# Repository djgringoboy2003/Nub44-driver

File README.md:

# NUBM44 laser diode driver

A constant-current driver for the Nichia NUBM44 high-power blue laser diode, from a single Li-ion cell,
targeting a 22 mm round PCB (plus a larger evaluation board) for PCBWay fabrication and assembly. Designed in KiCad 10 from version-controlled sources
(parameters, connectivity, placement), with automated checks and manufacturing export.

> **Safety:** the NUBM44 is a Class 4 laser source. Bench work needs a dummy load first, then appropriate
> eyewear, interlocks and a controlled area. This design is **not** validated on hardware (Gate G open).

## Status

- **Evaluation board (Variant B, 45 × 40 mm):** CAD complete (DRC 0/0/0/0), power-layout reviewed, DRAFT PCBWay
  review package generated. Release readiness: **DRAFT_REVIEW**; it becomes a PROTOTYPE_CANDIDATE once five human
  footprint/orientation reviews are recorded (`engineering/release/design-reviews.yaml`). Orders are placed by the
  owner by hand.
- **Compact board (Variant A, Ø 22 mm):** routing draft with 20 open signal connections, parked until the
  evaluation prototype has produced bench data (owner decision DD-27; strategy in
  `engineering/pcb-review-2026-10-26.md`). Its fabrication ZIP carries `DO_NOT_FABRICATE.txt`.
- **Separate budget-2s driver:** owner accepts two series Li-ion cells, unrestricted size and a £60 target
  per working unit. Electrical qualification has started (DD-30): independent numeric sources, conditional
  calculations and a preliminary ngspice loop study. Efficiency, UVLO and fault-control issues remain OPEN;
  no budget PCB/manufacturing package exists. Continue from the
  [implementation handover](engineering/budget-2s-design.md) and [plan](engineering/budget-driver-plan.md).
- **Physical validation (Gate G):** not started; it needs an assembled prototype and recorded bench data.
- **Firmware:** reworked after an independent audit (DD-28); 531 host checks, register-model tests of the hardware
  layer and a mutation check; not yet run on hardware.

**Ordering:** files and options for PCBWay and JLCPCB are in [documentation/ordering-guide.md](documentation/ordering-guide.md);
the pre-order review brief is [documentation/pre-order-review.md](documentation/pre-order-review.md).

Live state: [PROGRESS.md](PROGRESS.md) and the generated dashboard `reports/dashboard/index.html` (open it in a
browser). Agents start with [AGENTS.md](AGENTS.md); people with the
[developer guide](documentation/developer-guide.md). Audit: [reports/comprehensive-project-audit.md](reports/comprehensive-project-audit.md).

## Key specifications (original A/B design targets; see `engineering/requirements.md` for status)

| Item | Value |
|---|---|
| Input | 1 × Li-ion, 2.83–4.2 V at the board (18650/21700, ≥ 15 A CDR recommended) |
| Output | Constant current, 4.5 A (owner decision DD-36; 3.0 / 3.5 / 4.0 A by one resistor), compliance about 0.8–22 V |
| Converter | TI TPS552882 4-switch buck-boost, 595 kHz, 1.0 µH |
| Current regulation | 10 mΩ high-side shunt, INA186A2, ±3.6 % worst case (calculated) |
| Protection | Reverse polarity (P-FET), hardware UVLO, 4.8–5.2 A hardware current ceiling, hiccup short protection, open-load trip, interlock, default-off enable, thermal monitoring |
| Modes | Continuous, flash (2 Hz default); mode change by short power interruption or optional switch pad |
| Efficiency (estimated, 4.5 A) | 94.1 % at 4.0 V by model, 93.6 % with routed copper (target ≥ 93 %, owner DD-37); 90.3 % at 3.0 V |
| PCB | 4 layers, 1.6 mm, ENIG: Ø 22 mm compact board (Variant A) and 45 × 40 mm evaluation board (Variant B) |

## Getting started

```powershell
.\scripts\setup.ps1          # installs/repairs the toolchain (no admin rights needed)
.venv\Scripts\python.exe -m pytest tests                               # unit tests
.venv\Scripts\python.exe firmware\build.py --mutation                  # firmware host tests, ATtiny1616 build, mutation check
.venv\Scripts\python.exe automation\validation\validate.py            # register, readiness, dashboard (exit 1 = new or changed failure)
.venv\Scripts\python.exe automation\validation\validate.py --mode fast  # same checks without KiCad/ngspice/avr-gcc
```

Entry points:

```powershell
.\scripts\doctor.ps1
.\scripts\build.ps1 -Variant compact-22mm   # regenerates/reroutes; evaluation-board or all also supported
.\scripts\validate.ps1                     # tests + evidence register; fails while checks are unresolved
.\scripts\export-pcbway.ps1 -Variant evaluation-board
.\scripts\package.ps1                      # DRAFT review ZIP with source/evidence hashes
```

`build.ps1 -SkipRouting` reuses a session only when its DSN/SES hashes match. Read the actual gate state in
[the validation register](reports/validation-register.md) and the per-board level in
[release readiness](reports/release-readiness.md) (DRAFT_REVIEW, PROTOTYPE_CANDIDATE, MANUFACTURING_RELEASE; see the
[release checklist](documentation/release-checklist.md)). Export consistency and review packaging do not
release a board for manufacturing. CI (`.github/workflows/ci.yml`) runs the portable checks on Linux and the firmware
target build on Windows. Physical tests remain open. Battery polarity (centre spring B+, ring B−)
is marked on both boards' silkscreen.
See [assembly instructions](documentation/assembly.md) and [the bench plan](documentation/testing/test-plan.md).

If local PowerShell execution policy blocks a script, invoke it for that process with
`powershell.exe -NoProfile -ExecutionPolicy Bypass -File .\scripts\validate.ps1` (substitute the desired script).
The checked toolchain runs without changing machine policy or requiring administrator rights.

## Repository layout

See the map in [AGENTS.md](AGENTS.md#repository-map).

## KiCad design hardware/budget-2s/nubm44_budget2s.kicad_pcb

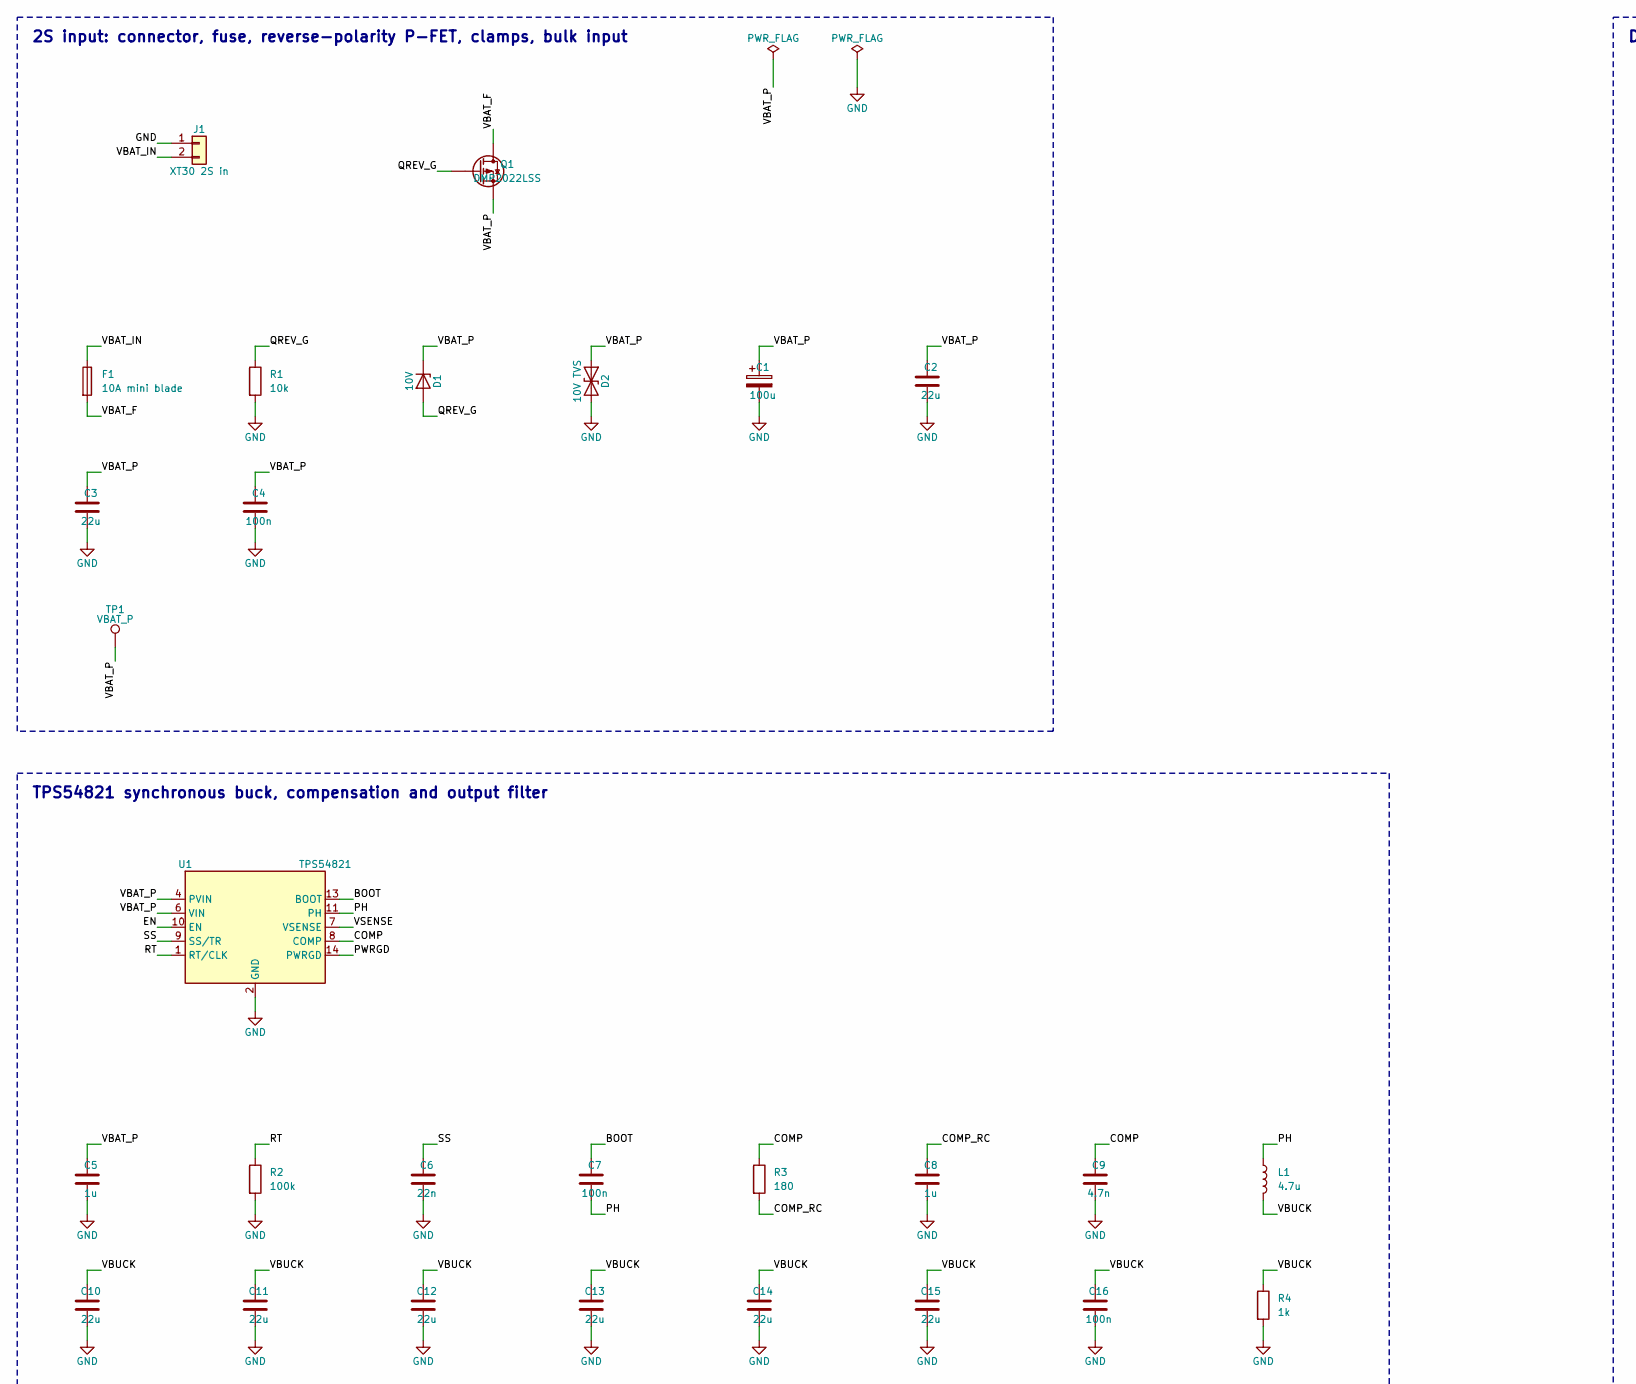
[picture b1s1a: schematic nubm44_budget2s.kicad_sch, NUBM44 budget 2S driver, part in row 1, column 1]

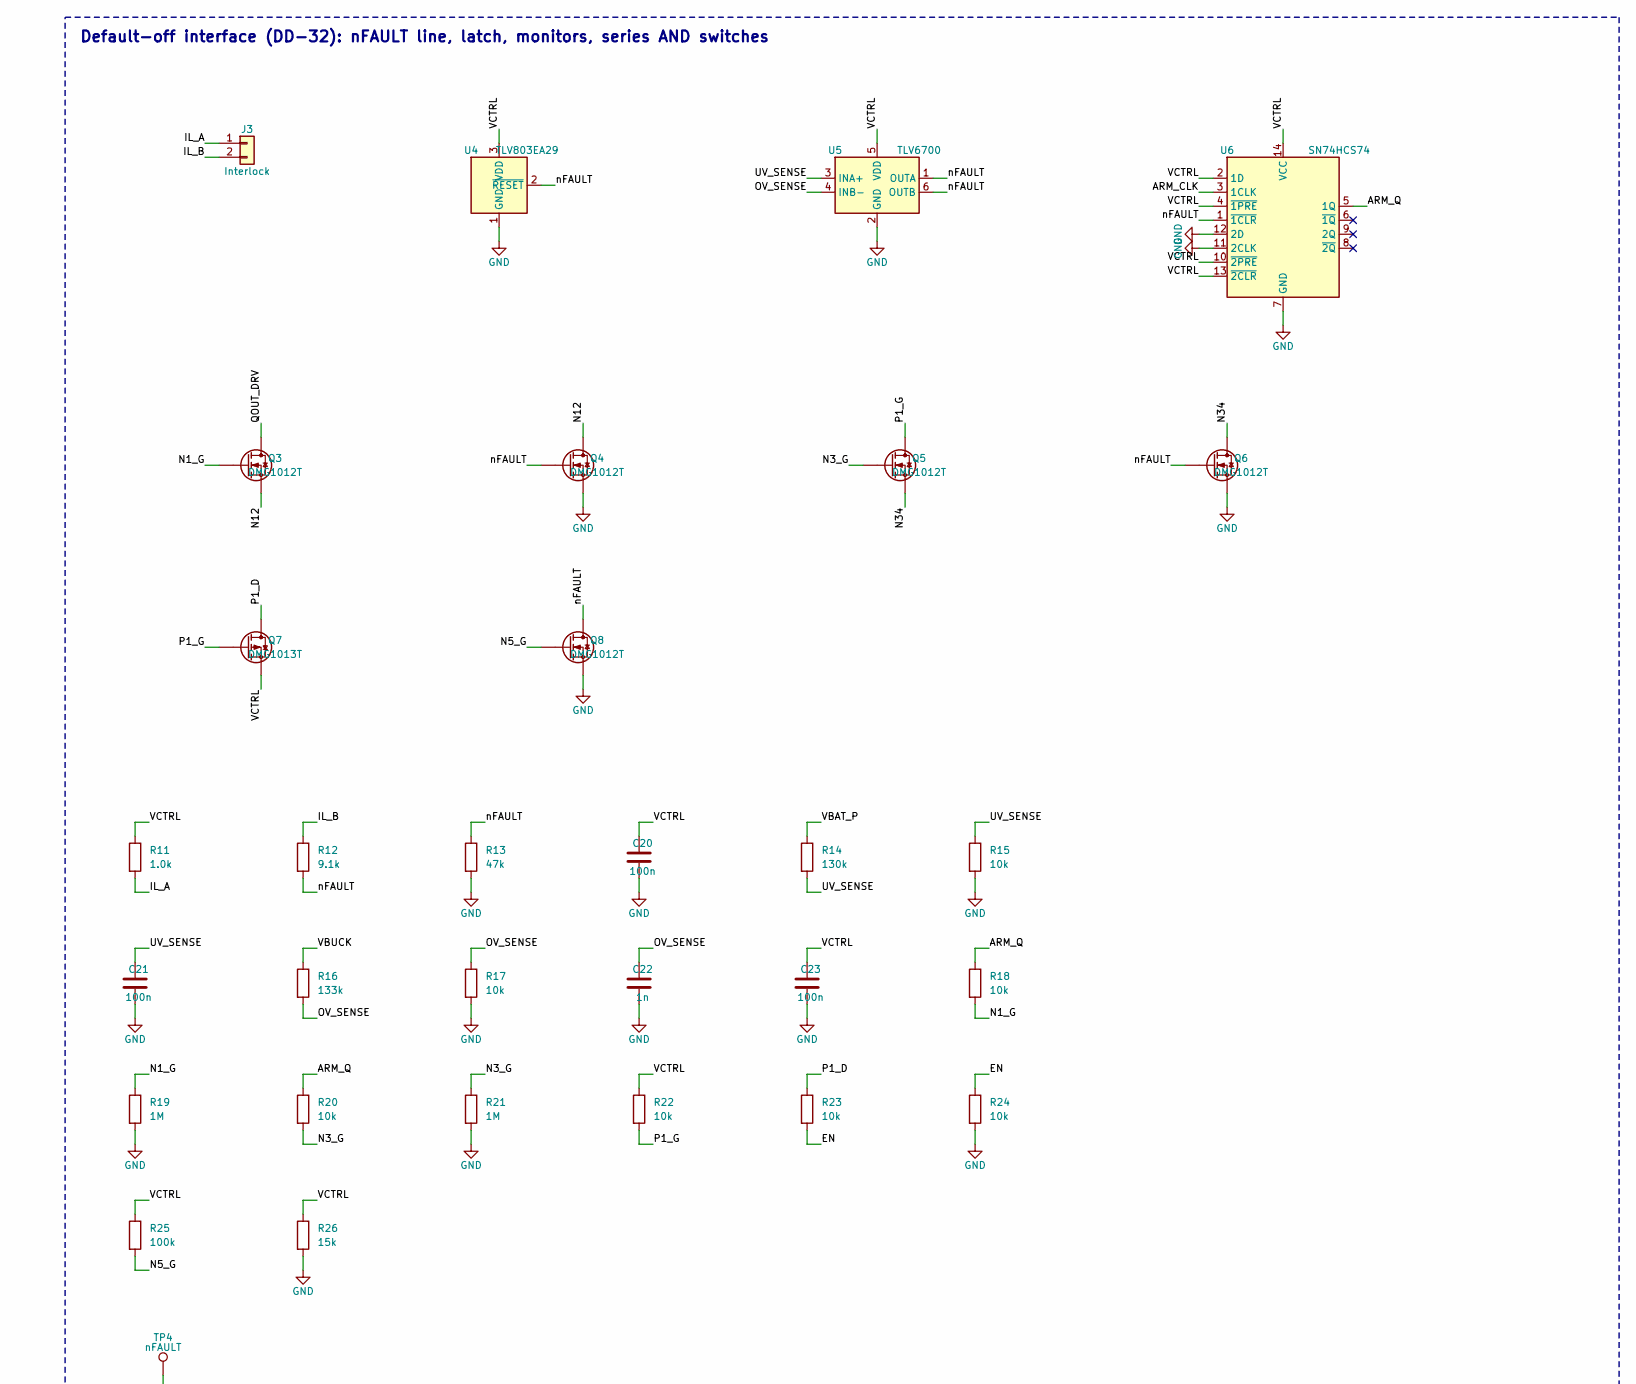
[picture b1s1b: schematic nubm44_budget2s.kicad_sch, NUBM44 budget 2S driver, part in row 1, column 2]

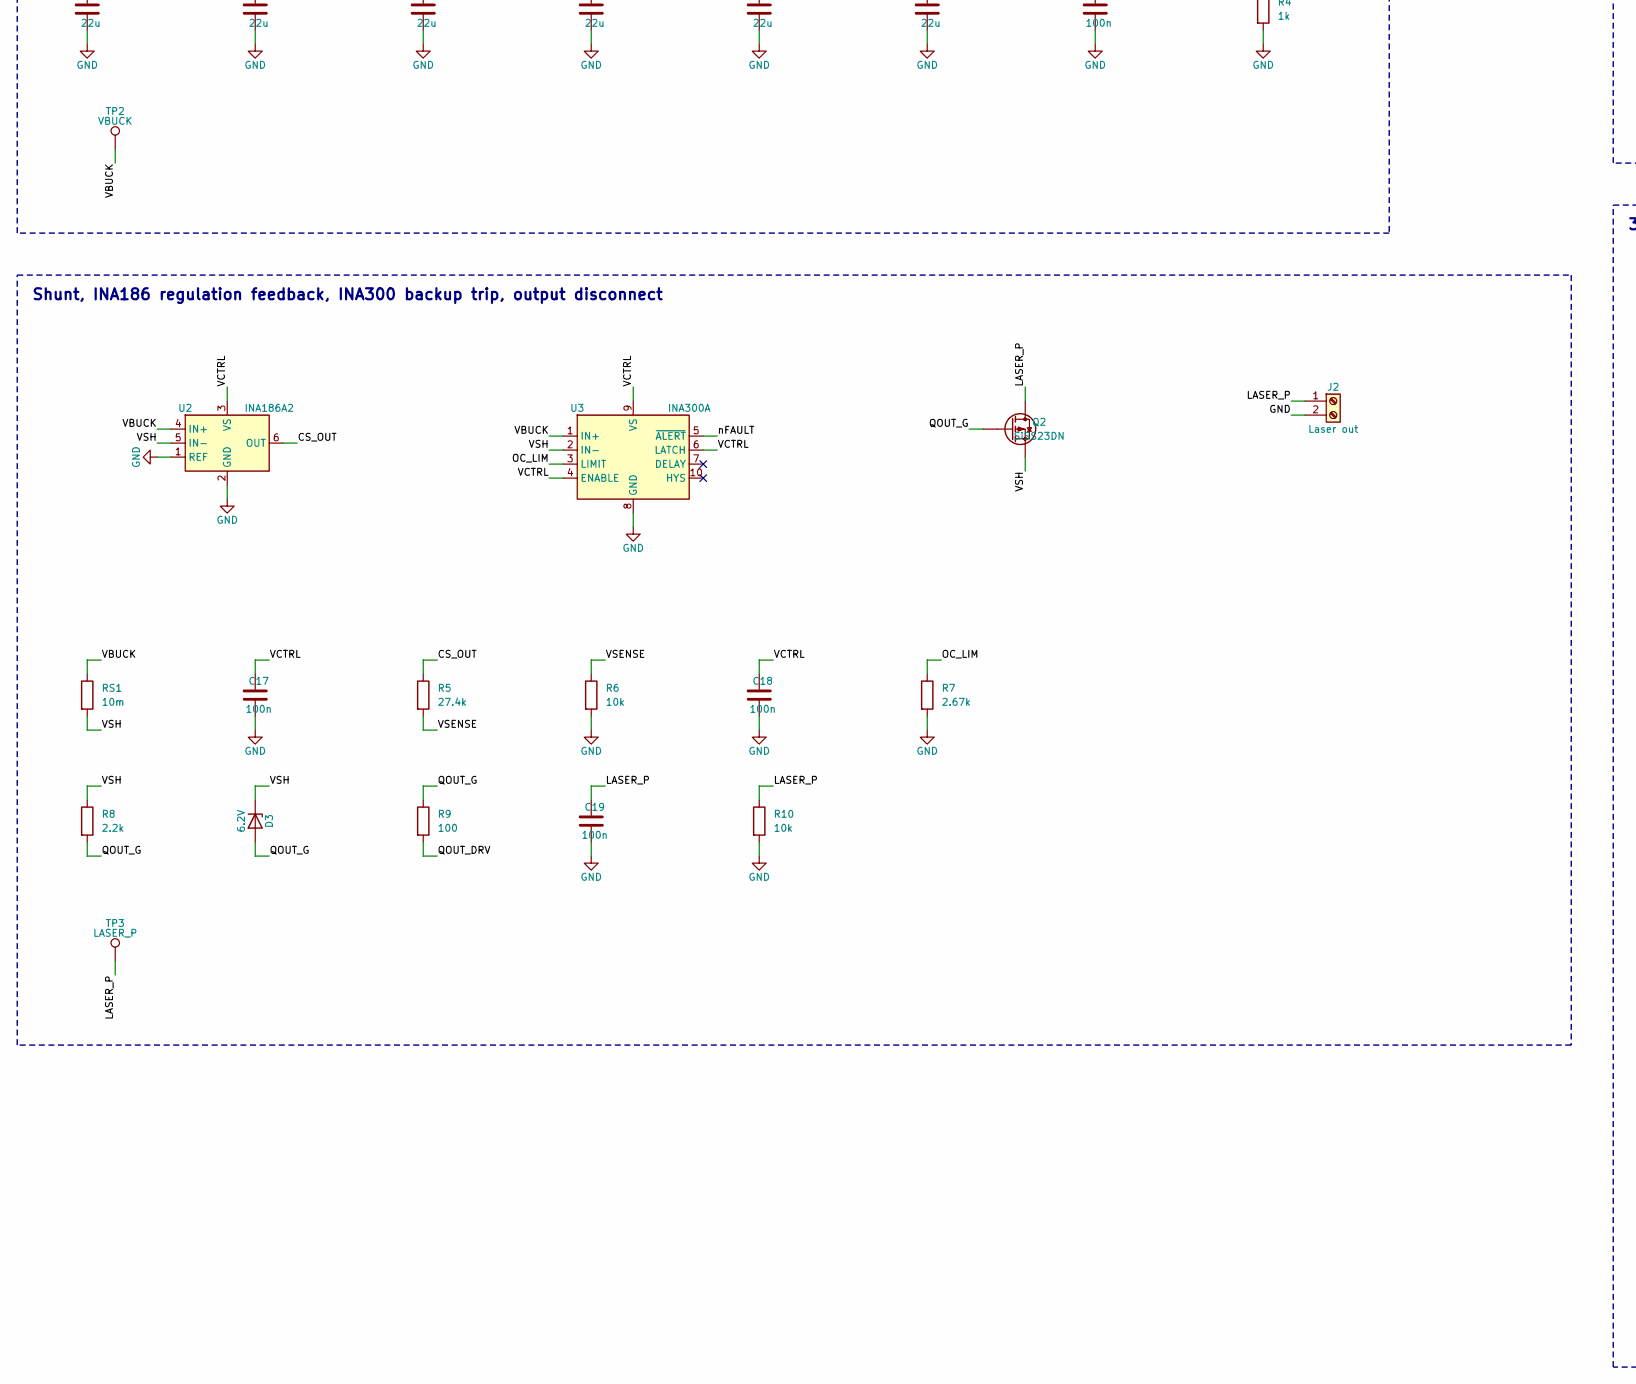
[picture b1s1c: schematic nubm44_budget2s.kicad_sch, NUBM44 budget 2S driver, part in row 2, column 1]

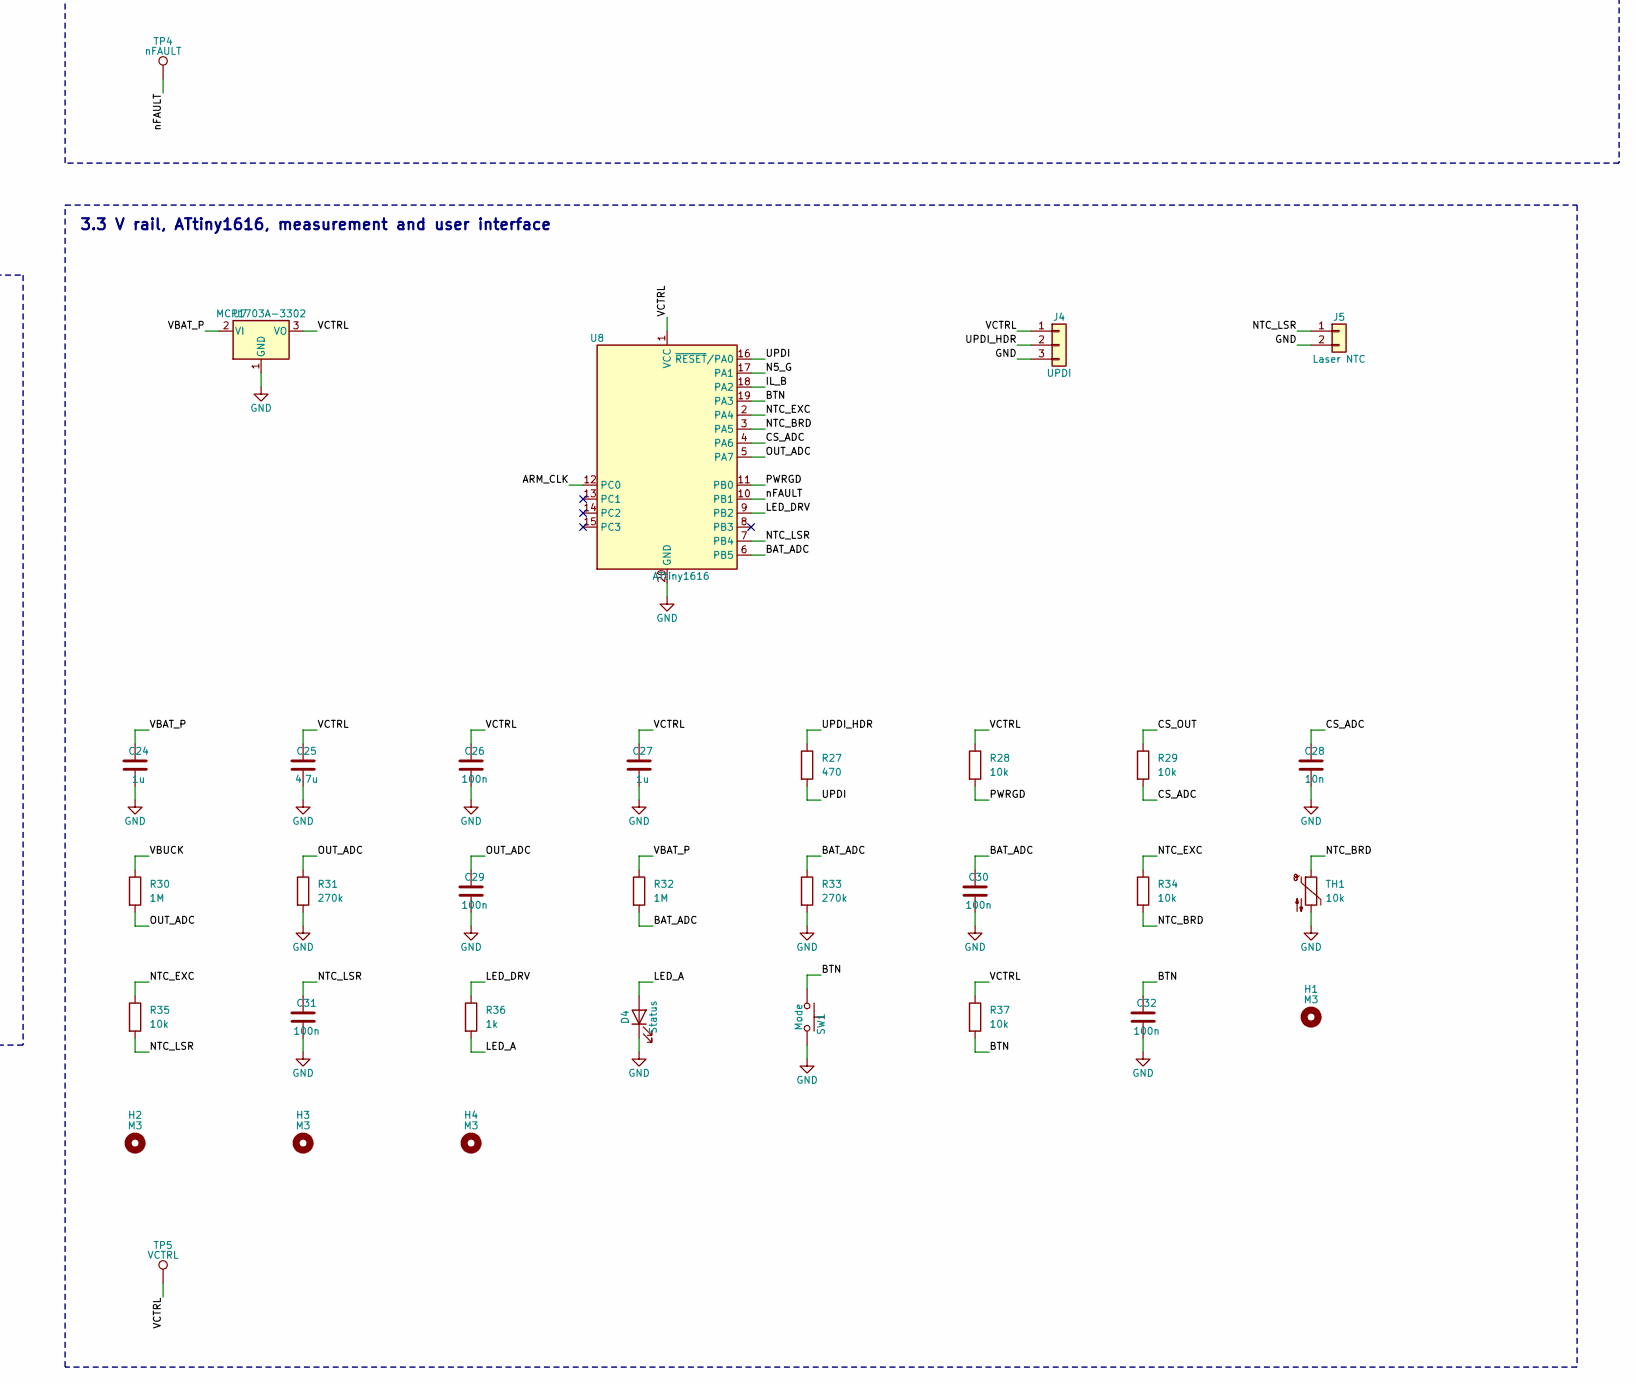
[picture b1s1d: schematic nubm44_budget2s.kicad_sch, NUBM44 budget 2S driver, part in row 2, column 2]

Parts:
C1: 100u; CP_Elec_6.3x7.7; MPN EMVL160ARA101MF80G
C2, C3, C10, C11, C12, C13, C14, C15: 22u; C_1206_3216Metric; MPN CL31A226KAHNNNE
C4, C7, C16, C17, C18, C19, C20, C21, C23, C26, C29, C30, C31, C32: 100n; C_0603_1608Metric; MPN CC0603KRX7R9BB104
C5, C24, C27: 1u; C_0603_1608Metric; MPN CL10A105KB8NNNC
C6: 22n; C_0603_1608Metric; MPN CL10B223KB8NNNC
C8: 1u; C_0603_1608Metric; MPN CL10B105KA8NNNC
C9: 4.7n; C_0603_1608Metric; MPN CC0603JRNPO9BN472
C22: 1n; C_0603_1608Metric; MPN 0603CG102J500NT
C25: 4.7u; C_0603_1608Metric; MPN CL10A475KO8NNNC
C28: 10n; C_0603_1608Metric; MPN 0603B103K500NT
D1: 10V; D_SOD-523; MPN BZX585-C10
D2: 10V TVS; D_SMA; MPN SMAJ10CA
D3: 6.2V; D_SOD-523; MPN BZX585-C6V2
D4: Status; LED_0805_2012Metric; MPN KT-0805Y
F1: 10A mini blade; Fuseholder_Blade_Mini_Keystone_3568; MPN 3568
H1, H2, H3, H4: M3; MountingHole_3.2mm_M3
J1: XT30 2S in; AMASS_XT30PW-M_1x02_P2.50mm_Horizontal; MPN XT30PW-M
J2: Laser out; TerminalBlock_MaiXu_MX126-5.0-02P_1x02_P5.00mm; MPN MX126-5.0-02P
J3: Interlock; JST_PH_B2B-PH-K_1x02_P2.00mm_Vertical; MPN B2B-PH-K-S
J4: UPDI; PinHeader_1x03_P2.54mm_Vertical; MPN 2.54-1*3P
J5: Laser NTC; JST_PH_B2B-PH-K_1x02_P2.00mm_Vertical; MPN B2B-PH-K-S
L1: 4.7u; L_Bourns_SRP1245A; MPN SRP1265A-4R7M
Q1: DMP2022LSS; SOIC-8_3.9x4.9mm_P1.27mm; MPN DMP2022LSS-13
Q2: SiSS23DN; Vishay_PowerPAK_1212-8_Single; MPN SISS23DN-T1-GE3
Q3, Q4, Q5, Q6, Q8: DMG1012T; SOT-523; MPN DMG1012T-7
Q7: DMG1013T; SOT-523; MPN DMG1013T-7
R1, R10, R18, R20, R22, R23, R24, R28, R29, R34, R35, R37: 10k; R_0603_1608Metric; MPN 0603WAF1002T5E
R2, R25: 100k; R_0603_1608Metric; MPN 0603WAF1003T5E
R3: 180; R_0603_1608Metric; MPN 0603WAF1800T5E
R4: 1k; R_0805_2012Metric; MPN 0805W8F1001T5E
R5: 27.4k; R_0603_1608Metric; MPN ERA-3AEB2742V
R6, R15, R17: 10k; R_0603_1608Metric; MPN ERA-3AEB103V
R7: 2.67k; R_0603_1608Metric; MPN TNPW06032K67BEEA
R8: 2.2k; R_0603_1608Metric; MPN 0603WAF2201T5E
R9: 100; R_0603_1608Metric; MPN 0603WAF1000T5E
R11: 1.0k; R_0603_1608Metric; MPN 0603WAF1001T5E
R12: 9.1k; R_0603_1608Metric; MPN RC0603FR-079K1L
R13: 47k; R_0603_1608Metric; MPN 0603WAF4702T5E
R14: 130k; R_0603_1608Metric; MPN ERA-3AEB134V
R16: 133k; R_0603_1608Metric; MPN RT0603BRD07133KL
R19, R21, R30, R32: 1M; R_0603_1608Metric; MPN 0603WAF1004T5E
R26: 15k; R_0603_1608Metric; MPN 0603WAF1502T5E
R27: 470; R_0603_1608Metric; MPN 0603WAF4700T5E
R31, R33: 270k; R_0603_1608Metric; MPN 0603WAF2703T5E
R36: 1k; R_0603_1608Metric; MPN 0603WAF1001T5E
RS1: 10m; R_2512_6332Metric; MPN WSL2512R0100FEA
SW1: Mode; SW_SPST_TL3342; MPN TL3342F160QG/TR
TH1: 10k; R_0603_1608Metric; MPN NCP18XH103F03RB
TP1: VBAT_P; TestPoint_Pad_D2.0mm
TP2: VBUCK; TestPoint_Pad_D2.0mm
TP3: LASER_P; TestPoint_Pad_D2.0mm
TP4: nFAULT; TestPoint_Pad_D2.0mm
TP5: VCTRL; TestPoint_Pad_D2.0mm
U1: TPS54821; TI_RHL0014A_VQFN-14-1EP_3.5x3.5mm_P0.5mm; MPN TPS54821RHLR
U2: INA186A2; SOT-363_SC-70-6; MPN INA186A2IDCKR
U3: INA300A; MSOP-10_3x3mm_P0.5mm; MPN INA300AIDGSR
U4: TLV803EA29; SOT-23; MPN TLV803EA29DBZR
U5: TLV6700; SOT-23-6; MPN TLV6700DDCR
U6: SN74HCS74; SOIC-14_3.9x8.7mm_P1.27mm; MPN SN74HCS74DR
U7: MCP1703A-3302; SOT-89-3; MPN MCP1703AT-3302E/MB
U8: ATtiny1616; SOIC-20W_7.5x12.8mm_P1.27mm; MPN ATTINY1616-SN

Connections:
/ARM_CLK: U6.3 (1CLK), U8.12 (PC0)
/ARM_Q: R18.1, R20.1, U6.5 (1Q)
/BAT_ADC: C30.1, R32.2, R33.1, U8.6 (PB5)
/BOOT: C7.1, U1.13 (BOOT)
/BTN: C32.1, R37.2, SW1.1, U8.19 (PA3)
/COMP: C9.1, R3.1, U1.8 (COMP)
/COMP_RC: C8.1, R3.2
/CS_ADC: C28.1, R29.2, U8.4 (PA6)
/CS_OUT: R5.1, R29.1, U2.6 (OUT)
/EN: R23.2, R24.1, U1.10 (EN)
/IL_A: J3.1, R11.2
/IL_B: J3.2, R12.1, U8.18 (PA2)
/LASER_P: C19.1, J2.1, Q2.5 (D), R10.1, TP3.1
/LED_A: D4.2 (A), R36.2
/LED_DRV: R36.1, U8.9 (PB2)
/N1_G: Q3.1 (G), R18.2, R19.1
/N3_G: Q5.1 (G), R20.2, R21.1
/N5_G: Q8.1 (G), R25.2, U8.17 (PA1)
/N12: Q3.2 (S), Q4.3 (D)
/N34: Q5.2 (S), Q6.3 (D)
/NTC_BRD: R34.2, TH1.1, U8.3 (PA5)
/NTC_EXC: R34.1, R35.1, U8.2 (PA4)
/NTC_LSR: C31.1, J5.1, R35.2, U8.7 (PB4)
/OC_LIM: R7.1, U3.3 (LIMIT)
/OUT_ADC: C29.1, R30.2, R31.1, U8.5 (PA7)
/OV_SENSE: C22.1, R16.2, R17.1, U5.4 (INB-)
/P1_D: Q7.3 (D), R23.1
/P1_G: Q5.3 (D), Q7.1 (G), R22.2
/PH: C7.2, L1.1, U1.11 (PH), U1.12 (PH)
/PWRGD: R28.2, U1.14 (PWRGD), U8.11 (PB0)
/QOUT_DRV: Q3.3 (D), R9.2
/QOUT_G: D3.2 (A), Q2.4 (G), R8.2, R9.1
/QREV_G: D1.2 (A), Q1.4 (G), R1.1
/RT: R2.1, U1.1 (RT/CLK)
/SS: C6.1, U1.9 (SS/TR)
/UPDI: R27.2, U8.16 (~RESET/PA0)
/UPDI_HDR: J4.2, R27.1
/UV_SENSE: C21.1, R14.2, R15.1, U5.3 (INA+)
/VBAT_F: F1.2, Q1.5 (D), Q1.6 (D), Q1.7 (D), Q1.8 (D)
/VBAT_IN: F1.1, J1.2
/VBAT_P: C1.1, C2.1, C3.1, C4.1, C5.1, C24.1, D1.1 (K), D2.1 (A1), Q1.1 (S), Q1.2 (S), Q1.3 (S), R14.1, R32.1, TP1.1, U1.4 (PVIN), U1.5 (PVIN), U1.6 (VIN), U7.2 (VI)
/VBUCK: C10.1, C11.1, C12.1, C13.1, C14.1, C15.1, C16.1, L1.2, R4.1, R16.1, R30.1, RS1.1, TP2.1, U2.4 (IN+), U3.1 (IN+)
/VCTRL: C17.1, C18.1, C20.1, C23.1, C25.1, C26.1, C27.1, J4.1, Q7.2 (S), R11.1, R22.1, R25.1, R26.1, R28.1, R37.1, TP5.1, U2.3 (VS), U3.4 (ENABLE), U3.6 (LATCH), U3.9 (VS), U4.3 (VDD), U5.5 (VDD), U6.2 (1D), U6.4 (~1PRE), U6.10 (~2PRE), U6.13 (~2CLR), U6.14 (VCC), U7.3 (VO), U8.1 (VCC)
/VSENSE: R5.2, R6.1, U1.7 (VSENSE)
/VSH: D3.1 (K), Q2.1 (S), Q2.2 (S), Q2.3 (S), R8.1, RS1.2, U2.5 (IN-), U3.2 (IN-)
/nFAULT: Q4.1 (G), Q6.1 (G), Q8.3 (D), R12.2, R13.1, TP4.1, U3.5 (~ALERT), U4.2 (~RESET), U5.1 (OUTA), U5.6 (OUTB), U6.1 (~1CLR), U8.10 (PB1)
GND: C1.2, C2.2, C3.2, C4.2, C5.2, C6.2, C8.2, C9.2, C10.2, C11.2, C12.2, C13.2, C14.2, C15.2, C16.2, C17.2, C18.2, C19.2, C20.2, C21.2, C22.2, C23.2, C24.2, C25.2, C26.2, C27.2, C28.2, C29.2, C30.2, C31.2, C32.2, D2.2 (A2), D4.1 (K), J1.1, J2.2, J4.3, J5.2, Q4.2 (S), Q6.2 (S), Q8.2 (S), R1.2, R2.2, R4.2, R6.2, R7.2, R10.2, R13.2, R15.2, R17.2, R19.2, R21.2, R24.2, R26.2, R31.2, R33.2, SW1.2, TH1.2, U1.2 (GND), U1.3 (GND), U1.15 (GND), U2.1 (REF), U2.2 (GND), U3.8 (GND), U4.1 (GND), U5.2 (GND), U6.7 (GND), U6.11 (2CLK), U6.12 (2D), U7.1 (GND), U8.20 (GND)

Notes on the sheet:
Default-off interface (DD-32): nFAULT line, latch, monitors, series AND switches
Shunt, INA186 regulation feedback, INA300 backup trip, output disconnect
3.3 V rail, ATtiny1616, measurement and user interface
TPS54821 synchronous buck, compensation and output filter
2S input: connector, fuse, reverse-polarity P-FET, clamps, bulk input

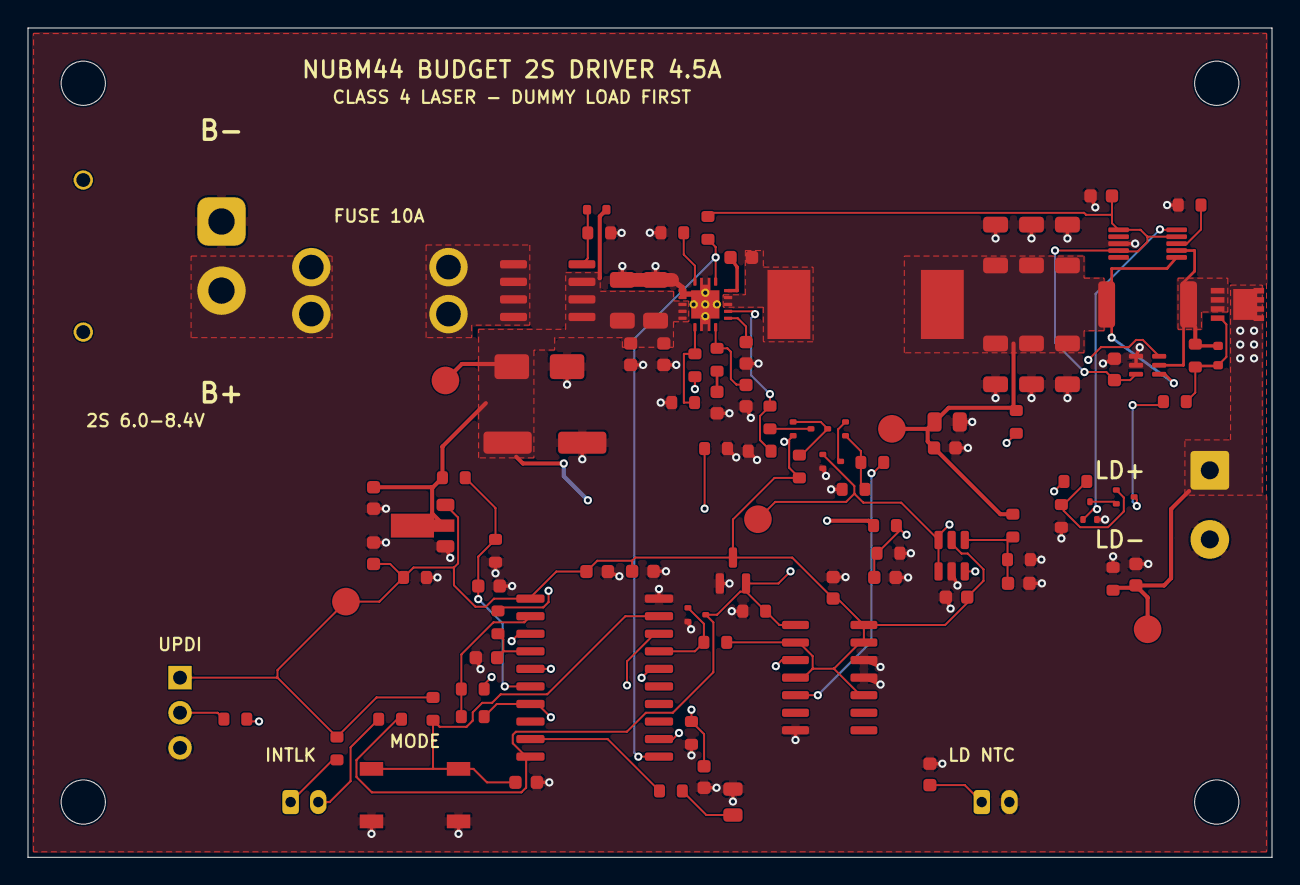
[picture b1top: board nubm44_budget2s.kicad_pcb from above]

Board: 4 copper layers, 90.0 x 60.0 mm, 108 parts (0 on the bottom side), 47 nets.
